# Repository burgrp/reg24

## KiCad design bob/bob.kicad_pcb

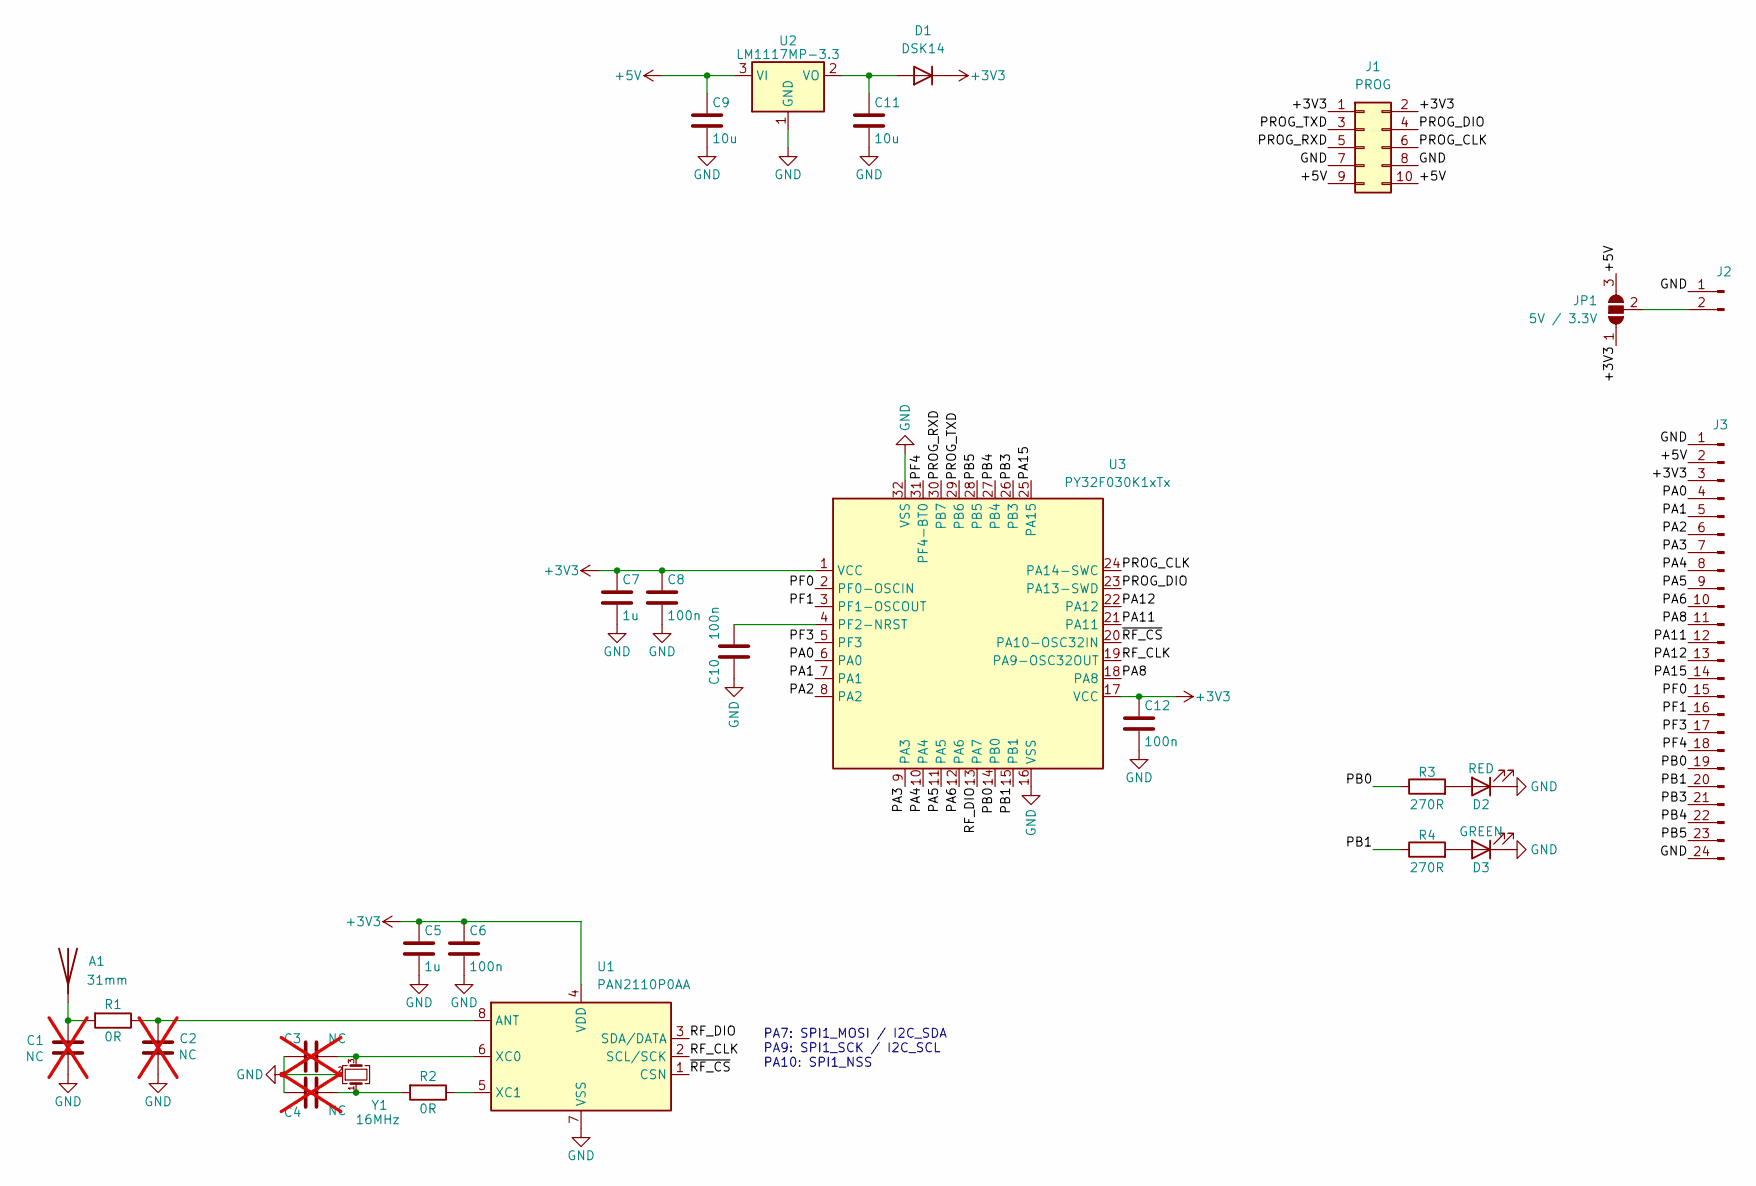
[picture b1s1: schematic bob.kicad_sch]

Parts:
A1: 31mm; Wire antena 2.4GHz
C1, C2, C3, C4: NC; C_0805_2012Metric; not fitted
C5, C7: 1u; C_0805_2012Metric
C6, C8, C10, C12: 100n; C_0805_2012Metric
C9, C11: 10u; C_0805_2012Metric
D1: DSK14; D_SOD-123
D2: RED; LED_0805_2012Metric
D3: GREEN; LED_0805_2012Metric
J1: PROG; PinHeader_2x05_P2.54mm_Vertical
J2: PWR; PinHeader_1x02_P2.54mm_Vertical
J3: BB; PinHeader_1x24_P2.54mm_Vertical
JP1: 5V / 3.3V; SolderJumper-3_P2.0mm_Open_TrianglePad1.0x1.5mm
R1, R2: 0R; R_0805_2012Metric
R3, R4: 270R; R_0805_2012Metric
U1: PAN2110P0AA; SOIC-8_3.9x4.9mm_P1.27mm
U2: LM1117MP-3.3; SOT-223-3_TabPin2
U3: PY32F030K1xTx; LQFP-32_7x7mm_P0.8mm
Y1: 16MHz; Crystal_SMD_3225-4Pin_3.2x2.5mm

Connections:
+3V3: C5.1, C6.1, C7.1, C8.1, C12.1, D1.1 (K), J1.1, J1.2, J3.3, JP1.1 (A), U1.4 (VDD), U3.1 (VCC), U3.17 (VCC)
+5V: C9.1, J1.9, J1.10, J3.2, JP1.3 (B), U2.3 (VI)
/PA0: J3.4, U3.6 (PA0)
/PA1: J3.5, U3.7 (PA1)
/PA2: J3.6, U3.8 (PA2)
/PA3: J3.7, U3.9 (PA3)
/PA4: J3.8, U3.10 (PA4)
/PA5: J3.9, U3.11 (PA5)
/PA6: J3.10, U3.12 (PA6)
/PA8: J3.11, U3.18 (PA8)
/PA11: J3.12, U3.21 (PA11)
/PA12: J3.13, U3.22 (PA12)
/PA15: J3.14, U3.25 (PA15)
/PB0: J3.19, R3.1, U3.14 (PB0)
/PB1: J3.20, R4.1, U3.15 (PB1)
/PB3: J3.21, U3.26 (PB3)
/PB4: J3.22, U3.27 (PB4)
/PB5: J3.23, U3.28 (PB5)
/PF0: J3.15, U3.2 (PF0-OSCIN)
/PF1: J3.16, U3.3 (PF1-OSCOUT)
/PF3: J3.17, U3.5 (PF3)
/PF4: J3.18, U3.31 (PF4-BT0)
/PROG_CLK: J1.6, U3.24 (PA14-SWC)
/PROG_DIO: J1.4, U3.23 (PA13-SWD)
/PROG_RXD: J1.5, U3.30 (PB7)
/PROG_TXD: J1.3, U3.29 (PB6)
/RF_CLK: U1.2 (SCL/SCK), U3.19 (PA9-OSC32OUT)
/RF_DIO: U1.3 (SDA/DATA), U3.13 (PA7)
/~RF_CS: U1.1 (CSN), U3.20 (PA10-OSC32IN)
GND: C1.1, C2.1, C3.1, C4.1, C5.2, C6.2, C7.2, C8.2, C9.2, C10.2, C11.2, C12.2, D2.1 (K), D3.1 (K), J1.7, J1.8, J2.1, J3.1, J3.24, U1.7 (VSS), U2.1 (GND), U3.16 (VSS), U3.32 (VSS), Y1.2 (G), Y1.4 (G)
unnamed: A1.1 (A), C1.2, R1.2
unnamed: C4.2, R2.2, Y1.1
unnamed: C11.1, D1.2 (A), U2.2 (VO)
unnamed: D2.2 (A), R3.2
unnamed: D3.2 (A), R4.2
unnamed: J2.2, JP1.2 (C)
unnamed: C2.2, R1.1, U1.8 (ANT)
unnamed: C3.2, U1.6 (XC0), Y1.3
unnamed: R2.1, U1.5 (XC1)
unnamed: C10.1, U3.4 (PF2-NRST)

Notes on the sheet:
PA7: SPI1_MOSI / I2C_SDA PA9: SPI1_SCK / I2C_SCL PA10: SPI1_NSS

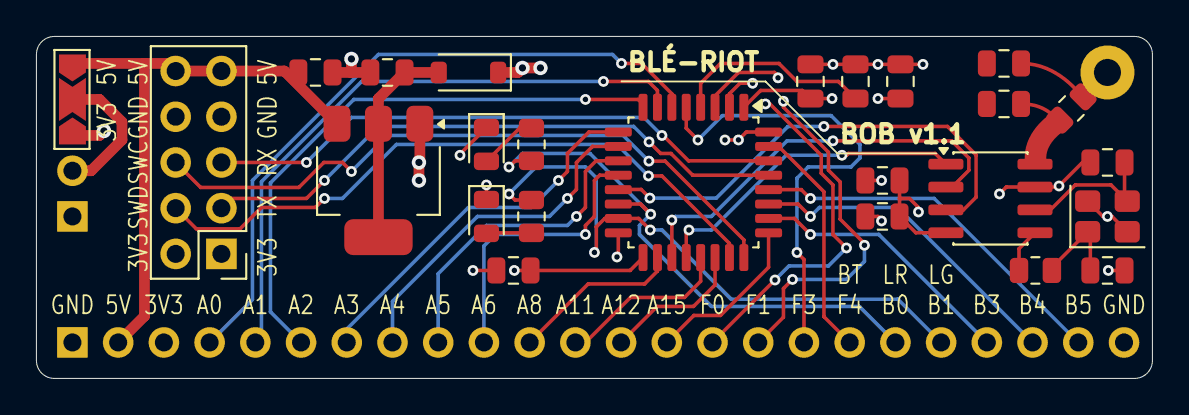
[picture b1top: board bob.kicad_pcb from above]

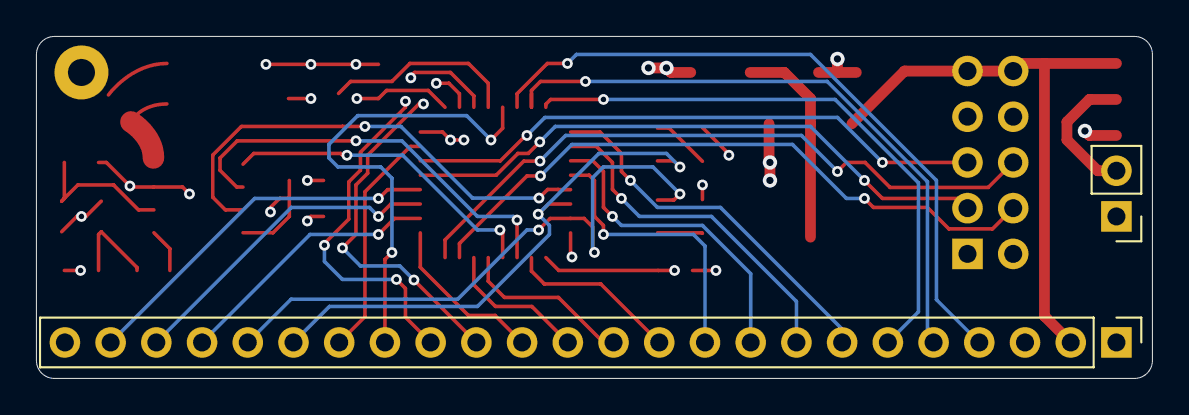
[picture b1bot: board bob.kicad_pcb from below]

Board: 4 copper layers, 62.0 x 19.0 mm, 28 parts (2 on the bottom side), 40 nets.
